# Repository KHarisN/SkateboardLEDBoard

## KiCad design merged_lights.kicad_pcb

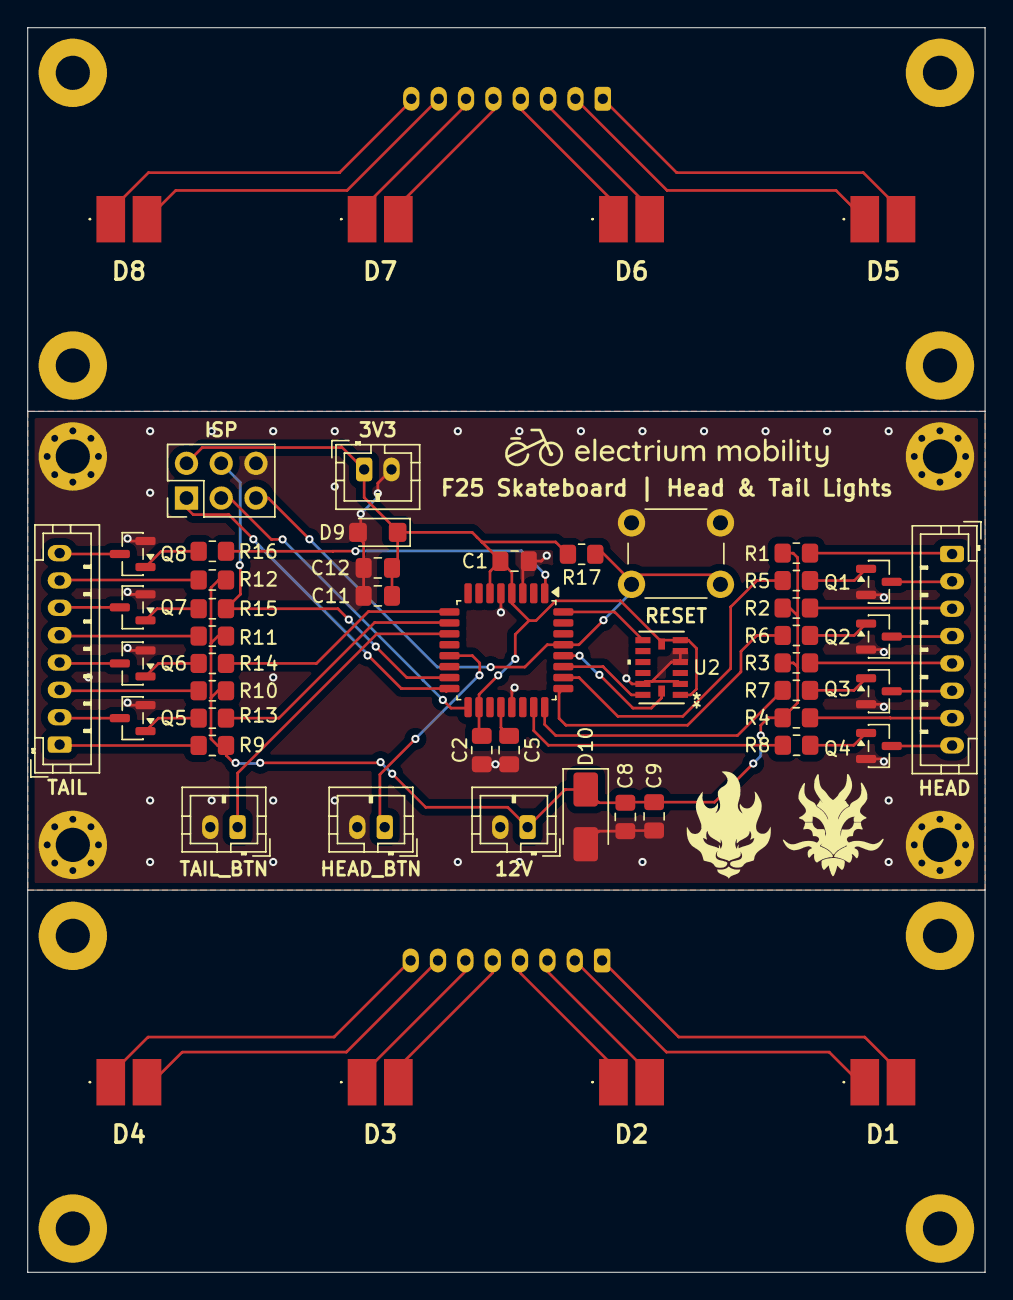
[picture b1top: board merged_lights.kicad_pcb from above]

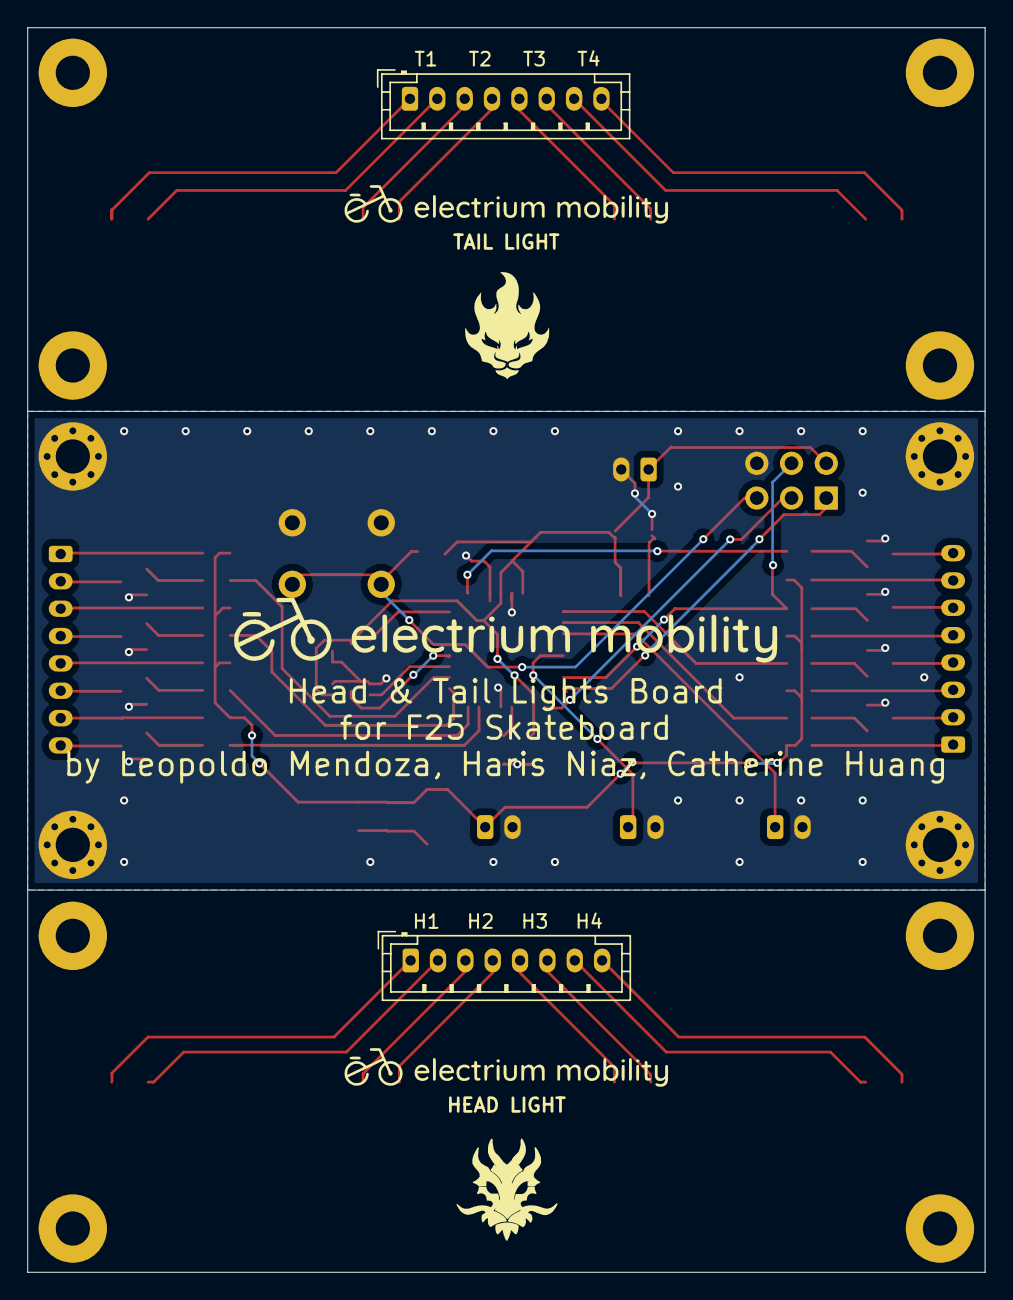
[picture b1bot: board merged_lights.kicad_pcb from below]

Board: 2 copper layers, 70.0 x 91.0 mm, 66 parts (2 on the bottom side), 60 nets.

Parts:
C1, C2, C5: 10uF; C_0805_2012Metric_Pad1.18x1.45mm_HandSolder
C8, C11: 47u; C_0805_2012Metric_Pad1.18x1.45mm_HandSolder
C9, C12: 100n; C_0805_2012Metric_Pad1.18x1.45mm_HandSolder
D1, D2, D3, D4: RED; ABEZD10CA3K65
D5, D6, D7, D8: RED; ABEZD03RA3
D9: SMF5V0A; D_SMF
D10: SMAJ15A; D_SMA
H1, H2, H3, H4: MountingHole_Pad; MountingHole_2.5mm_Pad_Via
H5, H6, H7, H8, H9, H10, H11, H12: MountingHole_Pad; MountingHole_2.5mm_Pad
J1, J2, J7, J9: Conn_01x08; JST_PH_B8B-PH-K_1x08_P2.00mm_Vertical
J3: AVR-ISP-6; PinHeader_2x03_P2.54mm_Vertical
J4, J5, J6, J8: Conn_01x02; JST_PH_B2B-PH-K_1x02_P2.00mm_Vertical
Q1, Q2, Q3, Q4, Q5, Q6, Q7, Q8: AO3400A; SOT-23
R1, R2, R3, R4, R9, R10, R11, R12: 100; R_0805_2012Metric_Pad1.20x1.40mm_HandSolder
R5, R6, R7, R8, R13, R14, R15, R16: 100R; R_0805_2012Metric_Pad1.20x1.40mm_HandSolder
R17: 10K; R_0805_2012Metric_Pad1.20x1.40mm_HandSolder
SW1: SW_Push; SW_PUSH_6mm
U1: ATmega328P-A; TQFP-32_7x7mm_P0.8mm
U2: ADXL345BCCZ; LGA_CC-14-1_ADI

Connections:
+3.3V: C1.1, C2.1, C11.1, C12.1, D9.1 (A1), J3.2 (VCC), J8.1, R17.2, U1.4 (VCC), U1.6 (VCC), U1.18 (AVCC), U2.1 (VDD_I/O), U2.6 (VS), U2.7 (*CS)
+12V: C8.1, C9.1, D10.1 (A1), J6.1, R1.1, R2.1, R3.1, R4.1, R9.1, R10.1, R11.1, R12.1
/Button1: J4.1, U1.11 (PD7)
/Button2: J5.1, U1.13 (PB1)
/HLB1.1: D1.2 (A), J1.1
/HLB1.2: D1.1 (K), J1.2
/HLB2.1: D2.2 (A), J1.3
/HLB2.2: D2.1 (K), J1.4
/HLB3.1: D3.2 (A), J1.5
/HLB3.2: D3.1 (K), J1.6
/HLB4.1: D4.2 (A), J1.7
/HLB4.2: D4.1 (K), J1.8
/HLED1: R5.1, U1.26 (PC3)
/HLED1.1: J2.1, R1.2
/HLED1.2: J2.2, Q1.3 (D)
/HLED2: R6.1, U1.25 (PC2)
/HLED2.1: J2.3, R2.2
/HLED2.2: J2.4, Q2.3 (D)
/HLED3: R7.1, U1.24 (PC1)
/HLED3.1: J2.5, R3.2
/HLED3.2: J2.6, Q3.3 (D)
/HLED4: R8.1, U1.23 (PC0)
/HLED4.1: J2.7, R4.2
/HLED4.2: J2.8, Q4.3 (D)
/INT: U1.32 (PD2), U2.8 (INT1)
/RESET: J3.5 (~RST), R17.1, SW1.1, U1.29 (~RESET/PC6)
/SCL: U1.28 (PC5), U2.14 (SCL/SCLK)
/SDA: U1.27 (PC4), U2.13 (SDA/SDI/SDIO)
/TLB1.1: D5.2 (A), J7.1
/TLB1.2: D5.1 (K), J7.2
/TLB2.1: D6.2 (A), J7.3
/TLB2.2: D6.1 (K), J7.4
/TLB3.1: D7.2 (A), J7.5
/TLB3.2: D7.1 (K), J7.6
/TLB4.1: D8.2 (A), J7.7
/TLB4.2: D8.1 (K), J7.8
/TLED1: R13.1, U1.10 (PD6)
/TLED1.1: J9.1, R9.2
/TLED1.2: J9.2, Q5.3 (D)
/TLED2: R14.1, U1.9 (PD5)
/TLED2.1: J9.3, R10.2
/TLED2.2: J9.4, Q6.3 (D)
/TLED3: J3.4 (MOSI), R15.1, U1.15 (PB3)
/TLED3.1: J9.5, R11.2
/TLED3.2: J9.6, Q7.3 (D)
/TLED4: R16.1, U1.1 (PD3)
/TLED4.1: J9.7, R12.2
/TLED4.2: J9.8, Q8.3 (D)
GND: C1.2, C2.2, C5.2, C8.2, C9.2, C11.2, C12.2, D9.2 (A2), D10.2 (A2), H1.1, H2.1, H3.1, H4.1, J3.6 (GND), J4.2, J5.2, J6.2, J8.2, Q1.2 (S), Q2.2 (S), Q3.2 (S), Q4.2 (S), Q5.2 (S), Q6.2 (S), Q7.2 (S), Q8.2 (S), SW1.2, U1.3 (GND), U1.5 (GND), U1.21 (GND), U2.2 (GND), U2.4 (GND), U2.5 (GND), U2.12 (SDO/ALT_ADDRESS)
unnamed: J3.1 (MISO), U1.16 (PB4)
unnamed: J3.3 (SCK), U1.17 (PB5)
unnamed: Q1.1 (G), R5.2
unnamed: Q2.1 (G), R6.2
unnamed: Q3.1 (G), R7.2
unnamed: Q4.1 (G), R8.2
unnamed: Q5.1 (G), R13.2
unnamed: Q6.1 (G), R14.2
unnamed: Q7.1 (G), R15.2
unnamed: Q8.1 (G), R16.2
unnamed: C5.1, U1.20 (AREF)
